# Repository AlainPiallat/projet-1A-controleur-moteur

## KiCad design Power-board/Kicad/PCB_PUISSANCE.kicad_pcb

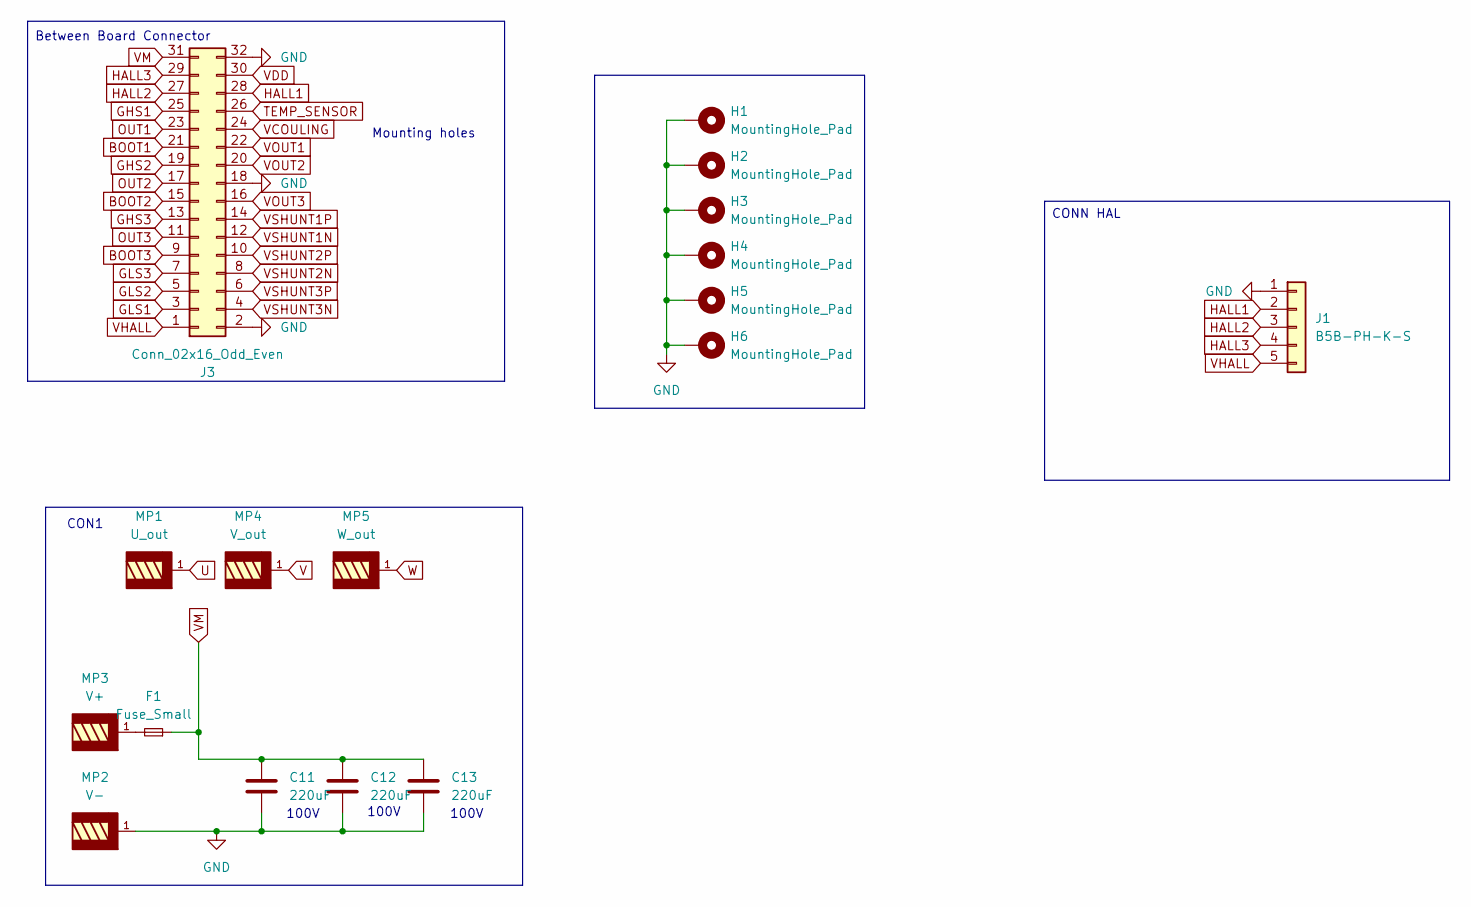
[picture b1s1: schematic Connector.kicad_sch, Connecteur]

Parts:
C11, C12, C13: 220uF; CP_Radial_D10.0mm_P5.00mm
F1: Fuse_Small; Fuse_3-140-177
H1, H2, H3, H4, H5, H6: MountingHole_Pad; MountingHole_3.2mm_M3_DIN965_Pad
J1: B5B-PH-K-S; JST_B5B-PH-K-S
J3: Conn_02x16_Odd_Even; PinHeader_2x16_P2.54mm_Vertical
MP1: U_out; Wurt
MP2: V-; Wurt
MP3: V+; Wurt
MP4: V_out; Wurt
MP5: W_out; Wurt

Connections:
BOOT1: J3.21; also elsewhere on the board
BOOT2: J3.15; also elsewhere on the board
BOOT3: J3.9; also elsewhere on the board
GHS1: J3.25; also elsewhere on the board
GHS2: J3.19; also elsewhere on the board
GHS3: J3.13; also elsewhere on the board
GLS1: J3.3; also elsewhere on the board
GLS2: J3.5; also elsewhere on the board
GLS3: J3.7; also elsewhere on the board
GND: C11.2, C12.2, C13.2, H1.1, H2.1, H3.1, H4.1, H5.1, H6.1, J1.1, J3.2, J3.18, J3.32, MP2.1, MP2.2, MP2.3, MP2.4; also elsewhere on the board
HALL1: J1.2, J3.28
HALL2: J1.3, J3.27
HALL3: J1.4, J3.29
unnamed: F1.2, MP3.1, MP3.2, MP3.3, MP3.4
OUT1: J3.23, MP1.1, MP1.2, MP1.3, MP1.4; also elsewhere on the board
OUT2: J3.17, MP4.1, MP4.2, MP4.3, MP4.4; also elsewhere on the board
OUT3: J3.11, MP5.1, MP5.2, MP5.3, MP5.4; also elsewhere on the board
TEMP_SENSOR: J3.26; also elsewhere on the board
VCOULING: J3.24
VDD: J3.30
VHALL: J1.5, J3.1; also elsewhere on the board
VM: C11.1, C12.1, C13.1, F1.1, J3.31; also elsewhere on the board
VOUT1: J3.22; also elsewhere on the board
VOUT2: J3.20; also elsewhere on the board
VOUT3: J3.16; also elsewhere on the board
VSHUNT1N: J3.12; also elsewhere on the board
VSHUNT1P: J3.14; also elsewhere on the board
VSHUNT2N: J3.8; also elsewhere on the board
VSHUNT2P: J3.10; also elsewhere on the board
VSHUNT3N: J3.4; also elsewhere on the board
VSHUNT3P: J3.6; also elsewhere on the board

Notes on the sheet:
CON1
100V
Mounting holes
Between Board Connector
CONN HAL

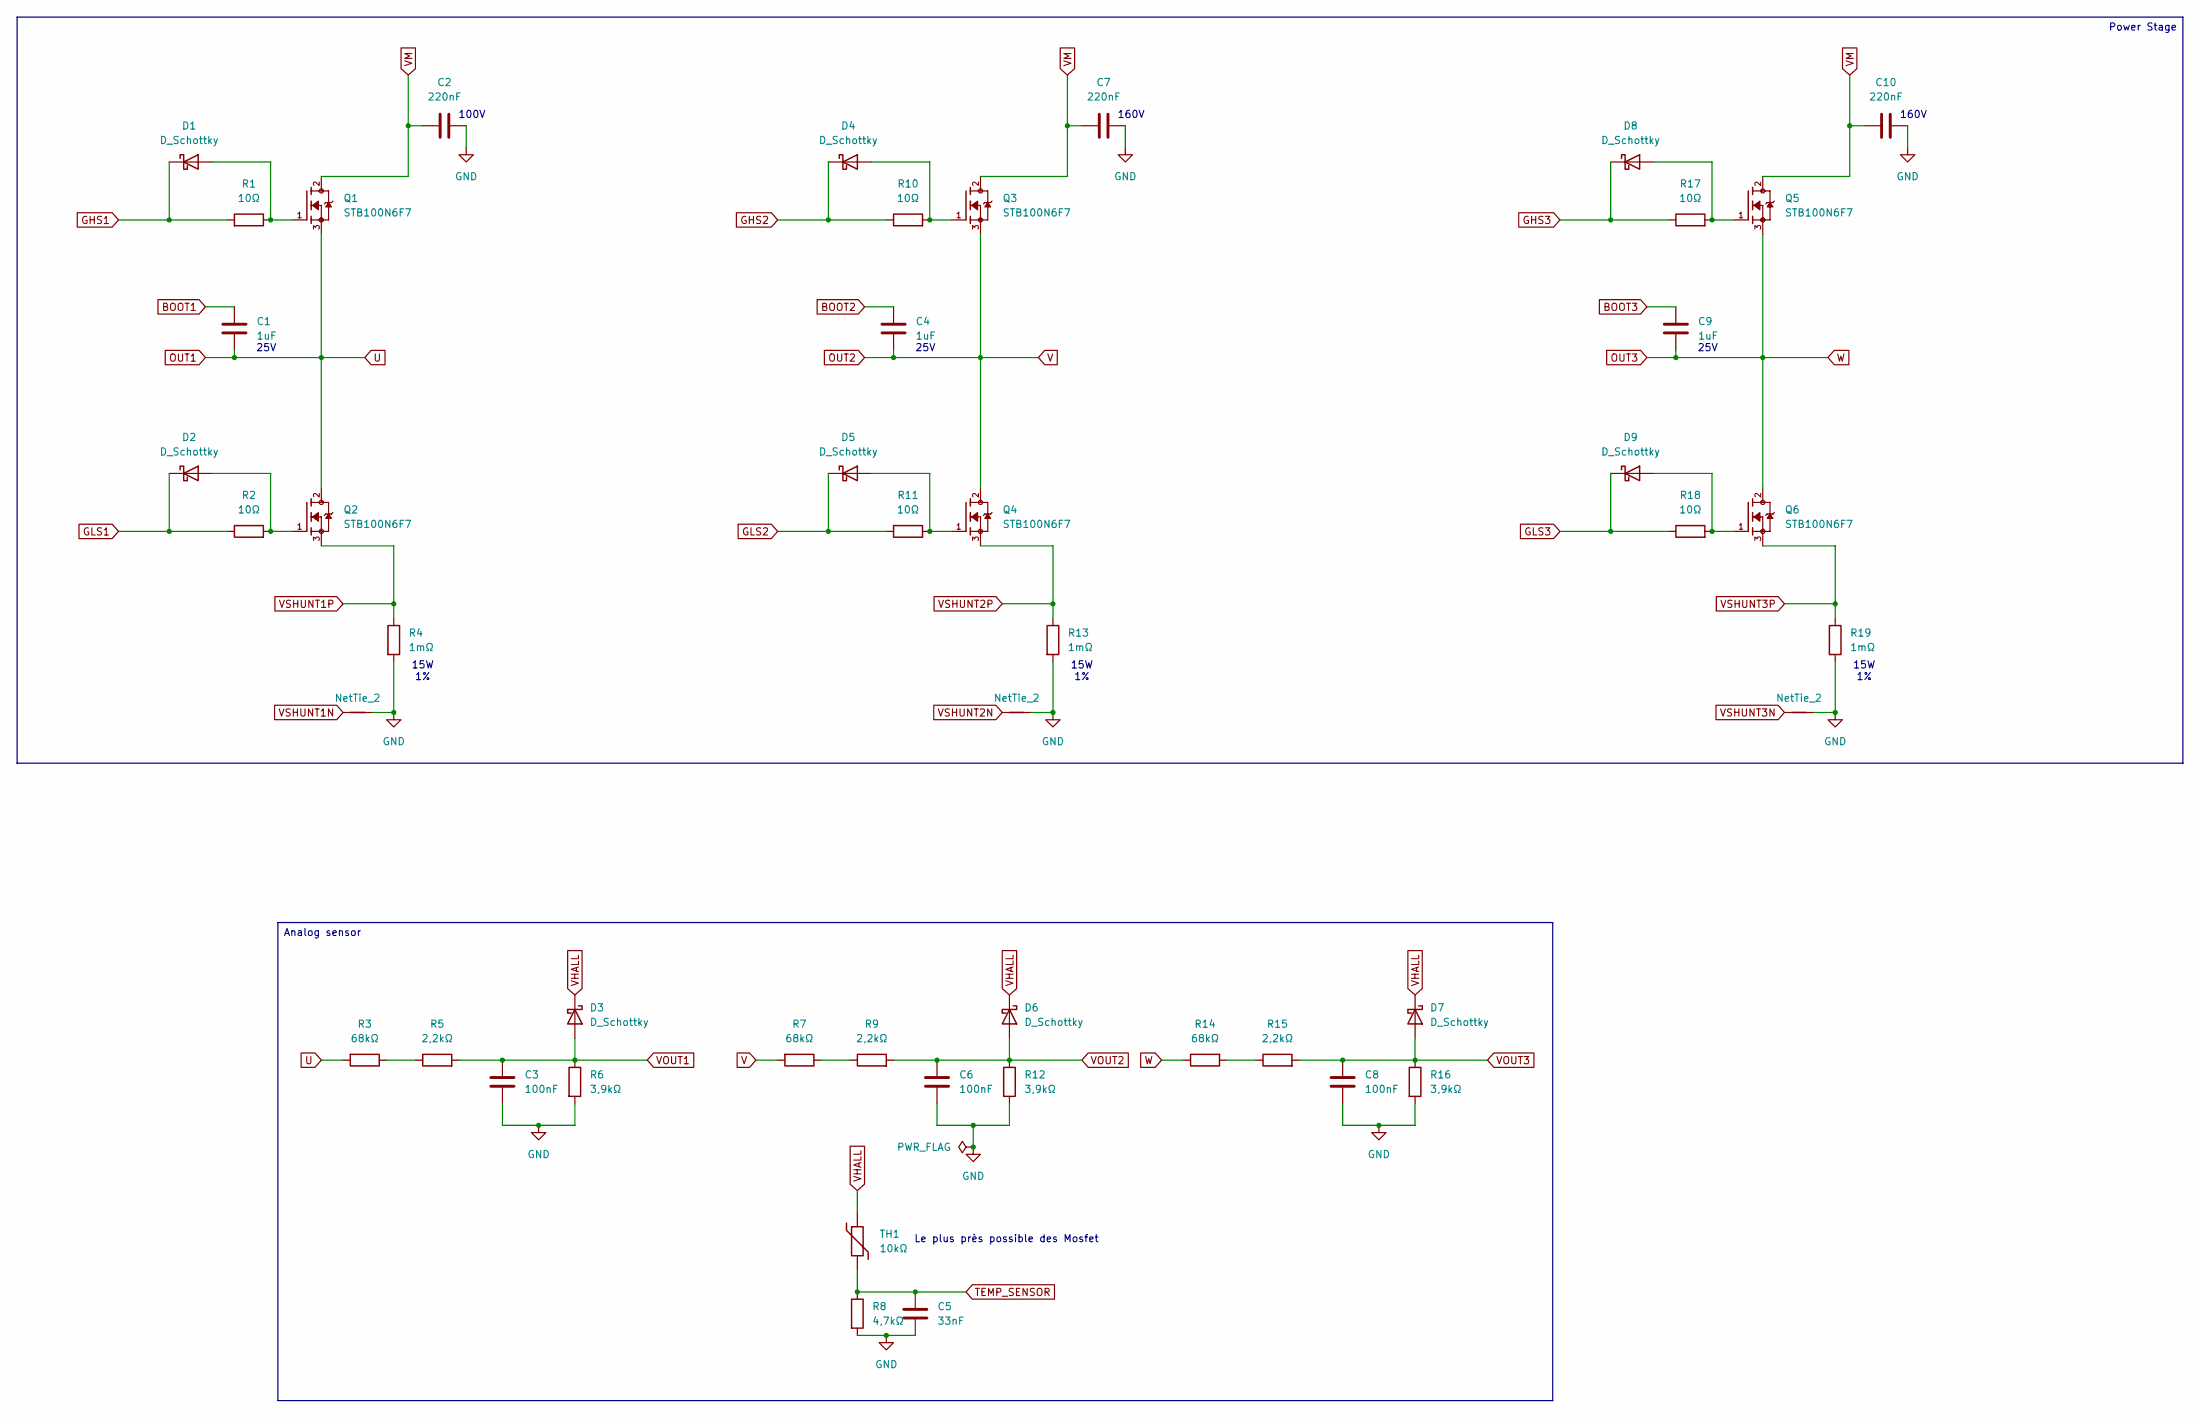
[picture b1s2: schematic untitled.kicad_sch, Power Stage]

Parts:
C1, C4, C9: 1uF; C_1206_3216Metric_Pad1.33x1.80mm_HandSolder
C2, C7, C10: 220nF; C_1210_3225Metric_Pad1.33x2.70mm_HandSolder
C3, C6, C8: 100nF; C_0805_2012Metric_Pad1.18x1.45mm_HandSolder
C5: 33nF; C_0805_2012Metric_Pad1.18x1.45mm_HandSolder
D1, D2, D3, D4, D5, D6, D7, D8, D9: D_Schottky; D_SOD-123
NT1, NT2, NT3: NetTie_2; NetTie-2_SMD_Pad0.5mm
Q1, Q2, Q3, Q4, Q5, Q6: STB100N6F7
R1, R2, R10, R11, R17, R18: 10Ω; R_1206_3216Metric_Pad1.30x1.75mm_HandSolder
R3, R7, R14: 68kΩ; R_1206_3216Metric_Pad1.30x1.75mm_HandSolder
R4, R13, R19: 1mΩ; PSR500HT
R5, R9, R15: 2,2kΩ; R_1206_3216Metric_Pad1.30x1.75mm_HandSolder
R6, R12, R16: 3,9kΩ; R_0805_2012Metric_Pad1.20x1.40mm_HandSolder
R8: 4,7kΩ; R_0805_2012Metric_Pad1.20x1.40mm_HandSolder
TH1: 10kΩ; THRMC1608X95N

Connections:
BOOT1: C1.1; also elsewhere on the board
BOOT2: C4.1; also elsewhere on the board
BOOT3: C9.1; also elsewhere on the board
GHS1: D1.1 (K), R1.2; also elsewhere on the board
GHS2: D4.1 (K), R10.1; also elsewhere on the board
GHS3: D8.1 (K), R17.1; also elsewhere on the board
GLS1: D2.1 (K), R2.1; also elsewhere on the board
GLS2: D5.1 (K), R11.1; also elsewhere on the board
GLS3: D9.1 (K), R18.1; also elsewhere on the board
GND: C2.2, C3.2, C5.2, C6.2, C7.2, C8.2, C10.2, NT1.2, NT2.2, NT3.2, R4.2, R6.2, R8.2, R12.2, R13.2, R16.2, R19.2; also elsewhere on the board
unnamed: D1.2 (A), Q1.1, R1.1
unnamed: D2.2 (A), Q2.1, R2.2
unnamed: D4.2 (A), Q3.1, R10.2
unnamed: D5.2 (A), Q4.1, R11.2
unnamed: D8.2 (A), Q5.1, R17.2
unnamed: D9.2 (A), Q6.1, R18.2
unnamed: R3.1, R5.1
unnamed: R7.1, R9.1
unnamed: R14.2, R15.1
OUT1: C1.2, Q1.3, Q2.2, R3.2; also elsewhere on the board
OUT2: C4.2, Q3.3, Q4.2, R7.2; also elsewhere on the board
OUT3: C9.2, Q5.3, Q6.2, R14.1; also elsewhere on the board
TEMP_SENSOR: C5.1, R8.1, TH1.2; also elsewhere on the board
VHALL: D3.1 (K), D6.1 (K), D7.1 (K), TH1.1; also elsewhere on the board
VM: C2.1, C7.1, C10.1, Q1.2, Q3.2, Q5.2; also elsewhere on the board
VOUT1: C3.1, D3.2 (A), R5.2, R6.1; also elsewhere on the board
VOUT2: C6.1, D6.2 (A), R9.2, R12.1; also elsewhere on the board
VOUT3: C8.1, D7.2 (A), R15.2, R16.1; also elsewhere on the board
VSHUNT1N: NT1.1; also elsewhere on the board
VSHUNT1P: Q2.3, R4.1; also elsewhere on the board
VSHUNT2N: NT2.1; also elsewhere on the board
VSHUNT2P: Q4.3, R13.1; also elsewhere on the board
VSHUNT3N: NT3.1; also elsewhere on the board
VSHUNT3P: Q6.3, R19.1; also elsewhere on the board

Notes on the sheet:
160V
25V
15W 1%
Le plus près possible des Mosfet
100V
Analog sensor
Power Stage

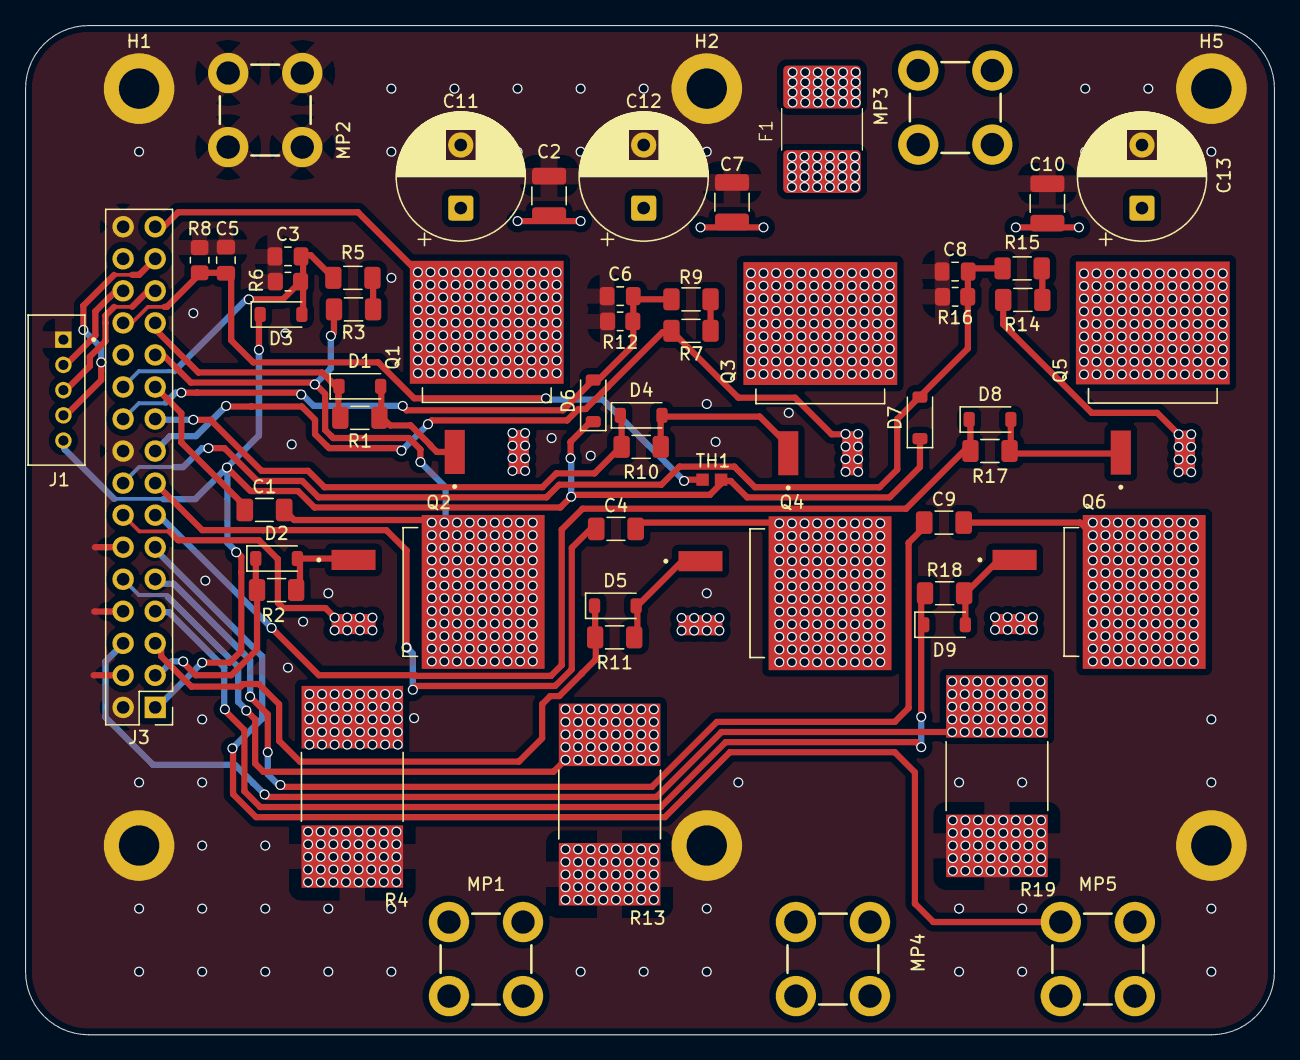
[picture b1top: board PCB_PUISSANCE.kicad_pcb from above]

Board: 2 copper layers, 99.0 x 80.0 mm, 65 parts (0 on the bottom side), 38 nets.

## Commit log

2026-05-30 Create Power-bord
2026-05-30 Create Connecteurs
2026-05-30 Create Schematics
2026-05-30 Rename Power-board/Connecteurs/Rapport_Schematics.md to Power-board/Power/Dimensionnement_des_composants/Readme.md
    Charles tu ranges pas bien ta chambre
2026-05-30 Rename Power-board/Power/Schematic/Readme.md to Power-board/Power/Readme.md
2026-05-30 Rename CR_Carte_Puissance_connecteur_hugo.md to Readme.md
    Changement du nom du fichier pour qu'il s'ouvre directement
2026-05-30 Rename Power-board/Connecteurs/Schematics.pdf to Power-board/Schematics.pdf
    Déplacement des schémas au bon endroit
2026-05-30 Delete Power-board/Power/Kicad directory
    Déplacement fichiers kicad
